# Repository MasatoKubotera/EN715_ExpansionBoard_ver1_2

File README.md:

<html lang="en">
  <head>
    <meta charset="uft-8">
    <meta name="author" content="Masato Kubotera">
  </head>
  <body>
    <h1>EN715 Expansion Board Ver. 1.2</h1>
    <h2>About EN715 Expansion Board</h2>
    <p>
      The EN715 Expansion Board is a circuit board to expand the functions of the Carrier Board for NVIDIA Jetson manufactured by AverMedia.<br>
      <br>
      Note that this is Ver. 1.2. For other versions, please refer to the following repositories.
      <ul>
        <li><a href="https://github.com/MasatoKubotera/EN715_ExpansionBoard_ver1_0">EN715 Expansion Board Ver. 1.0</a></li>
        <li><a href="https://github.com/MasatoKubotera/EN715_ExpansionBoard_ver1_1">EN715 Expansion Board Ver. 1.1</a></li>
      </ul>
      <h2>About Ver. 1.2</h2>
      <table>
        <tr>
          <td>
            <div align="center">
              under construction<br>
              
            </div>
          </td>
          <td>
            <div align="center">
              under construction<br>
              
            </div>
          </td>
        </tr>
        <tr>
          <td>
            <div align="center">
              PCB preview image
            </div>
          </td>
          <td>
            <div align="center">
              After component mounting
            </div>
          </td>    
        </tr>
      </table>
    <h2>Repository Contents</h2>
    <p>
    <dl>
      <dt>\image</dt>
      <dd>PCB preview images and capture of design screen</dd>
      <dt>\libraries</dt>
      <dd>Libraries used in Autodesk Eagle design</dd>
      <dt>Schematic.pdf</dt>
      <dd>Circuit diagram of this product</dd>
      <dt>BOM.txt</dt>
      <dd>Parts lists output from design data</dd>
      <dt>.brd</dt>
      <dd>Board wiring design file by Autodesk Eagle</dd>
      <dt>.sch</dt>
      <dd>Schematic design file by Autodesk Eagle</dd>
      <!--
      <dt>Gerber_data.zip</dt>
      <dd>Zip folder of Gerber format files for PCB manufacturing requests.</dd>
      -->
      <dt>LICENSE</dt>
      <dd>This is a license to use this product. Please confirm before use.</dd>
      <dt>.gitignore</dt>
      <dd>File to exclude cache files from management.</dd>
    </dl>
    </p>
    <h2>Documentation</h2>
      <p>
        <h3>BOM</h3>
          <table>
            <thead>
              <tr>
                <th> Eagle Design Parts # </th>
                <th> Q'ty </th>
                <th> Mfr. Product # </th>
                <th> Supplier </th>
                <th> Description </th>
              </tr>
            </thead>
            <tbody>
              <tr>
                <td> C1, C2, C3 </td>
                <td> 3 </td>
                <td> GRM188R6YA106MA73 </td>
                <td> <a href="https://akizukidenshi.com/catalog/g/gP-13161/">Akizuki</a> </td>
                <td> Multilayer Ceramic Capacitors SMD/SMT 10uF 35V 20% 0603 </td>
              </tr>
              <tr>
                <td> C4 </td>
                <td> 1 </td>
                <td> GRM188B11H103KA01 </td>
                <td> <a href="https://akizukidenshi.com/catalog/g/gP-13387/">Akizuki</a> </td>
                <td> Multilayer Ceramic Capacitors SMD/SMT 0.01uF 50V 10% 0603 </td>
              </tr>
              <tr>
                <td> C5, C6 </td>
                <td> 2 </td>
                <td> C1608C0G1H220J080AA </td>
                <td> <a href="https://www.mouser.jp/ProductDetail/TDK/C1608C0G1H220J080AA?qs=NRhsANhppD%2FvEAPMU6eN6g%3D%3D">Mouser</a> </td>
                <td> Multilayer Ceramic Capacitors SMD/SMT 22pF 50V 5% 0603 </td>
              </tr>
              <tr>
                <td> CH1 </td>
                <td> 1 </td>
                <td> FH-2x10SG </td>
                <td> <a href="https://akizukidenshi.com/catalog/g/gC-00083/">Akizuki</a> </td>
                <td> 2.54mm Pin Socket, 2 Row, 20 Pin </td>
              </tr>
              <tr>
                <td> CR1 </td>
                <td> 1 </td>
                <td> FA-238V 12.0000MB-K3 </td>
                <td> <a href="https://akizukidenshi.com/catalog/g/gP-05225/">Akizuki</a> </td>
                <td> Crystals 12.0000MHz 50ppm 10pF -40C +85C </td>
              </tr>
              <tr>
                <td> D1, D2, D3, D4, D5, D6, D7, D8, D9, D10 </td>
                <td> 10 </td>
                <td> CG0603MLC-05E </td>
                <td> <a href="https://www.mouser.jp/ProductDetail/Bourns/CG0603MLC-05E?qs=lDok7oSghXVLNKMK69q%252BFQ%3D%3D">Mouser</a> </td>
                <td> ESD Protectors 5V 0603 </td>
              </tr>
              <tr>
                <td> F1 </td>
                <td> 1 </td>
                <td> MF-MSMF050-2 </td>
                <td> <a href="https://www.mouser.jp/ProductDetail/Bourns/MF-MSMF050-2?qs=t3shhpq1i1DZ7OBD5kLNoA%3D%3D">Mouser</a> </td>
                <td> PTC Resettable Fuses 15V .5A-HD 100A MAX </td>
              </tr>
              <tr>
                <td> FL1, FL2, FL3, FL4, FL5 </td>
                <td> 5 </td>
                <td> BLM18SD220SN1D </td>
                <td> <a href="https://www.mouser.jp/ProductDetail/Murata-Electronics/BLM18SD220SN1D?qs=glnLrWX4TPq%2Fm8%2FdPQltLg%3D%3D">Mouser</a> </td>
                <td> Ferrite Beads 22 OHM 0603 </td>
              </tr>
              <tr>
                <td> IC1 </td>
                <td> 1 </td>
                <td> FE1.1S </td>
                <td> <a href="https://www.aitendo.com/product/16185">aitendo</a> </td>
                <td> USB Interface IC USB 2.0 Hi-Speed 4 Port Hub Controller </td>
              </tr>
              <tr>
                <td> LED1 </td>
                <td> 1 </td>
                <td> 150060VS86000 </td>
                <td> <a href="https://www.mouser.jp/ProductDetail/Wurth-Elektronik/150060VS86000?qs=GedFDFLaBXGW9qOjzZ1Hmw%3D%3D">Mouser</a> </td>
                <td> Standard LEDs - SMD Green 2V 20mA 573nm 0603 </td>
              </tr>
              <tr>
                <td> LED2, LED3, LED4, LED5, LED6 </td>
                <td> 5 </td>
                <td> 150060YS75000 </td>
                <td> <a href="https://www.mouser.jp/ProductDetail/Wurth-Elektronik/150060YS75000?qs=LlUlMxKIyB0nKmwefHgtZw%3D%3D">Mouser</a> </td>
                <td> Standard LEDs - SMD Yellow 2V 20mA 590nm 0603 </td>
              </tr>
              <tr>
                <td> M1 </td>
                <td> 1 </td>
                <td> SEN-15335 </td>
                <td> <a href="https://www.mouser.jp/ProductDetail/SparkFun/SEN-15335?qs=uwxL4vQweFMcls1MYZT00A%3D%3D">Mouser</a> </td>
                <td> 9-Axis MotionTracking Device Module </td>
              </tr>
              <tr>
                <td> M1 </td>
                <td> 1 </td>
                <td> 6604S-40 </td>
                <td> <a href="https://akizukidenshi.com/catalog/g/gP-01591/">Akizuki</a> </td>
                <td> 2.54mm Pin Socket Strip, Single Row </td>
              </tr>
              <tr>
                <td> M1 </td>
                <td> 1 </td>
                <td> PHA-1x40SG </td>
                <td> <a href="https://akizukidenshi.com/catalog/g/gC-06631/">Akizuki</a> </td>
                <td> 2.54mm Pin Header Strip, Straight, Single Row </td>
              </tr>
              <tr>
                <td> R1, R3, R4, R5 </td>
                <td> 4 </td>
                <td> RC0603FR-101KL </td>
                <td> <a href="https://www.mouser.jp/ProductDetail/YAGEO/RC0603FR-101KL?qs=EiqXWrxQq63MM0wzm69ZKg%3D%3D">Mouser</a> </td>
                <td> Thick Film Resistors - SMD 1 kOhms 100-200mW 1% 0603 </td>
              </tr>
              <tr>
                <td> R2 </td>
                <td> 1 </td>
                <td> RC0603FR-102K7L </td>
                <td> <a href="https://www.mouser.jp/ProductDetail/YAGEO/RC0603FR-102K7L?qs=Iqe6t0HYRD6Xaw3IgOqXnw%3D%3D">Mouser</a> </td>
                <td> Thick Film Resistors - SMD 2.7 kOhms 100-200 mW 1% 0603 </td>
              </tr>
              <tr>
                <td> USB1 </td>
                <td> 1 </td>
                <td> MUSB-5B-NE-S175 </td>
                <td> <a href="https://akizukidenshi.com/catalog/g/gC-05843/">Akizuki</a> </td>
                <td> Mini USB Connector 5P B type, Female, SMT type, without standoff </td>
              </tr>
              <tr>
                <td> USB2, USB3, USB4, USB5 </td>
                <td> 4 </td>
                <td> USB1046-GF-0190-L-B-A </td>
                <td> <a href="https://www.mouser.jp/ProductDetail/640-USB1046GF0190LBA">Mouser</a> </td>
                <td> USB Connectors USB2.0 A, Top Mount, SMT </td>
              </tr>
            </tbody>
          </table>
        <!--
        <h3>PCB Fabrication</h3>
          PCB(Printed Circuit Board) manufacturing was outsourced to <a href="https://www.elecrow.com/pcb-manufacturing.html">Elecrow</a>.<br>
          The custom specifications are as follows.
          <ul>
            <li>Layer : 2 layers</li>
            <li>Dimensions : 87 x 50</li>
            <li>PCB Qty : 10</li>
            <li>Different PCB Design : 1eg</li>
            <li>PCB Thickness : 1.6</li>
            <li>PCB Color : Black</li>
            <li>Surface Finish : HASL Lead Free</li>
            <li>Castellated Hole : No</li>
            <li>Copper Weight : 1oz</li>
            <li>PCB Stencil : Stencil 15cm X 15cm no frame</li>
          </ul>
          The data used to order fabrication are as follows.
          <ul>
            <li>Eagle design rule : <a href="https://www.elecrow.com/download/Elecrow_PCB_eagle_rule.zip">Elecrow Eagle Design Rule</a></li>
            <li>Eagle CAM file : <a href="https://www.elecrow.com/download/Elecrow_Gerber_Generater_DrillAlign.zip">Elecrow CAM file</a></li>
            <li>Gerber format data : <a href="/Gerber_data.zip">Gerber_data.zip</a></li>
          </ul>
      </p>
      -->
    <h2>Contact</h2>
    <p>
    If you have any questions, please contact MasatoKubotera, the product's designer, by E-mail.<br>
    E-mail : <a href="mailto:masatokubotera06@yahoo.co.jp">masatokubotera06@yahoo.co.jp</a>
    </p>
    <h2>License Information</h2>
    <p>
      This product is open source.<br>
      Please review the <a href="/LICENSE">LICENSE file</a> for license information.<br>
      <br>
      <strong>EN715 Expansion Board Ver. 1.2</strong> by Masato Kubotera is licensed under a <a href="http://creativecommons.org/licenses/by-nc-sa/4.0/">Creative Commons Attribution-NonCommercial-ShareAlike 4.0 International License</a>.
    </p>
  </body>
</html>

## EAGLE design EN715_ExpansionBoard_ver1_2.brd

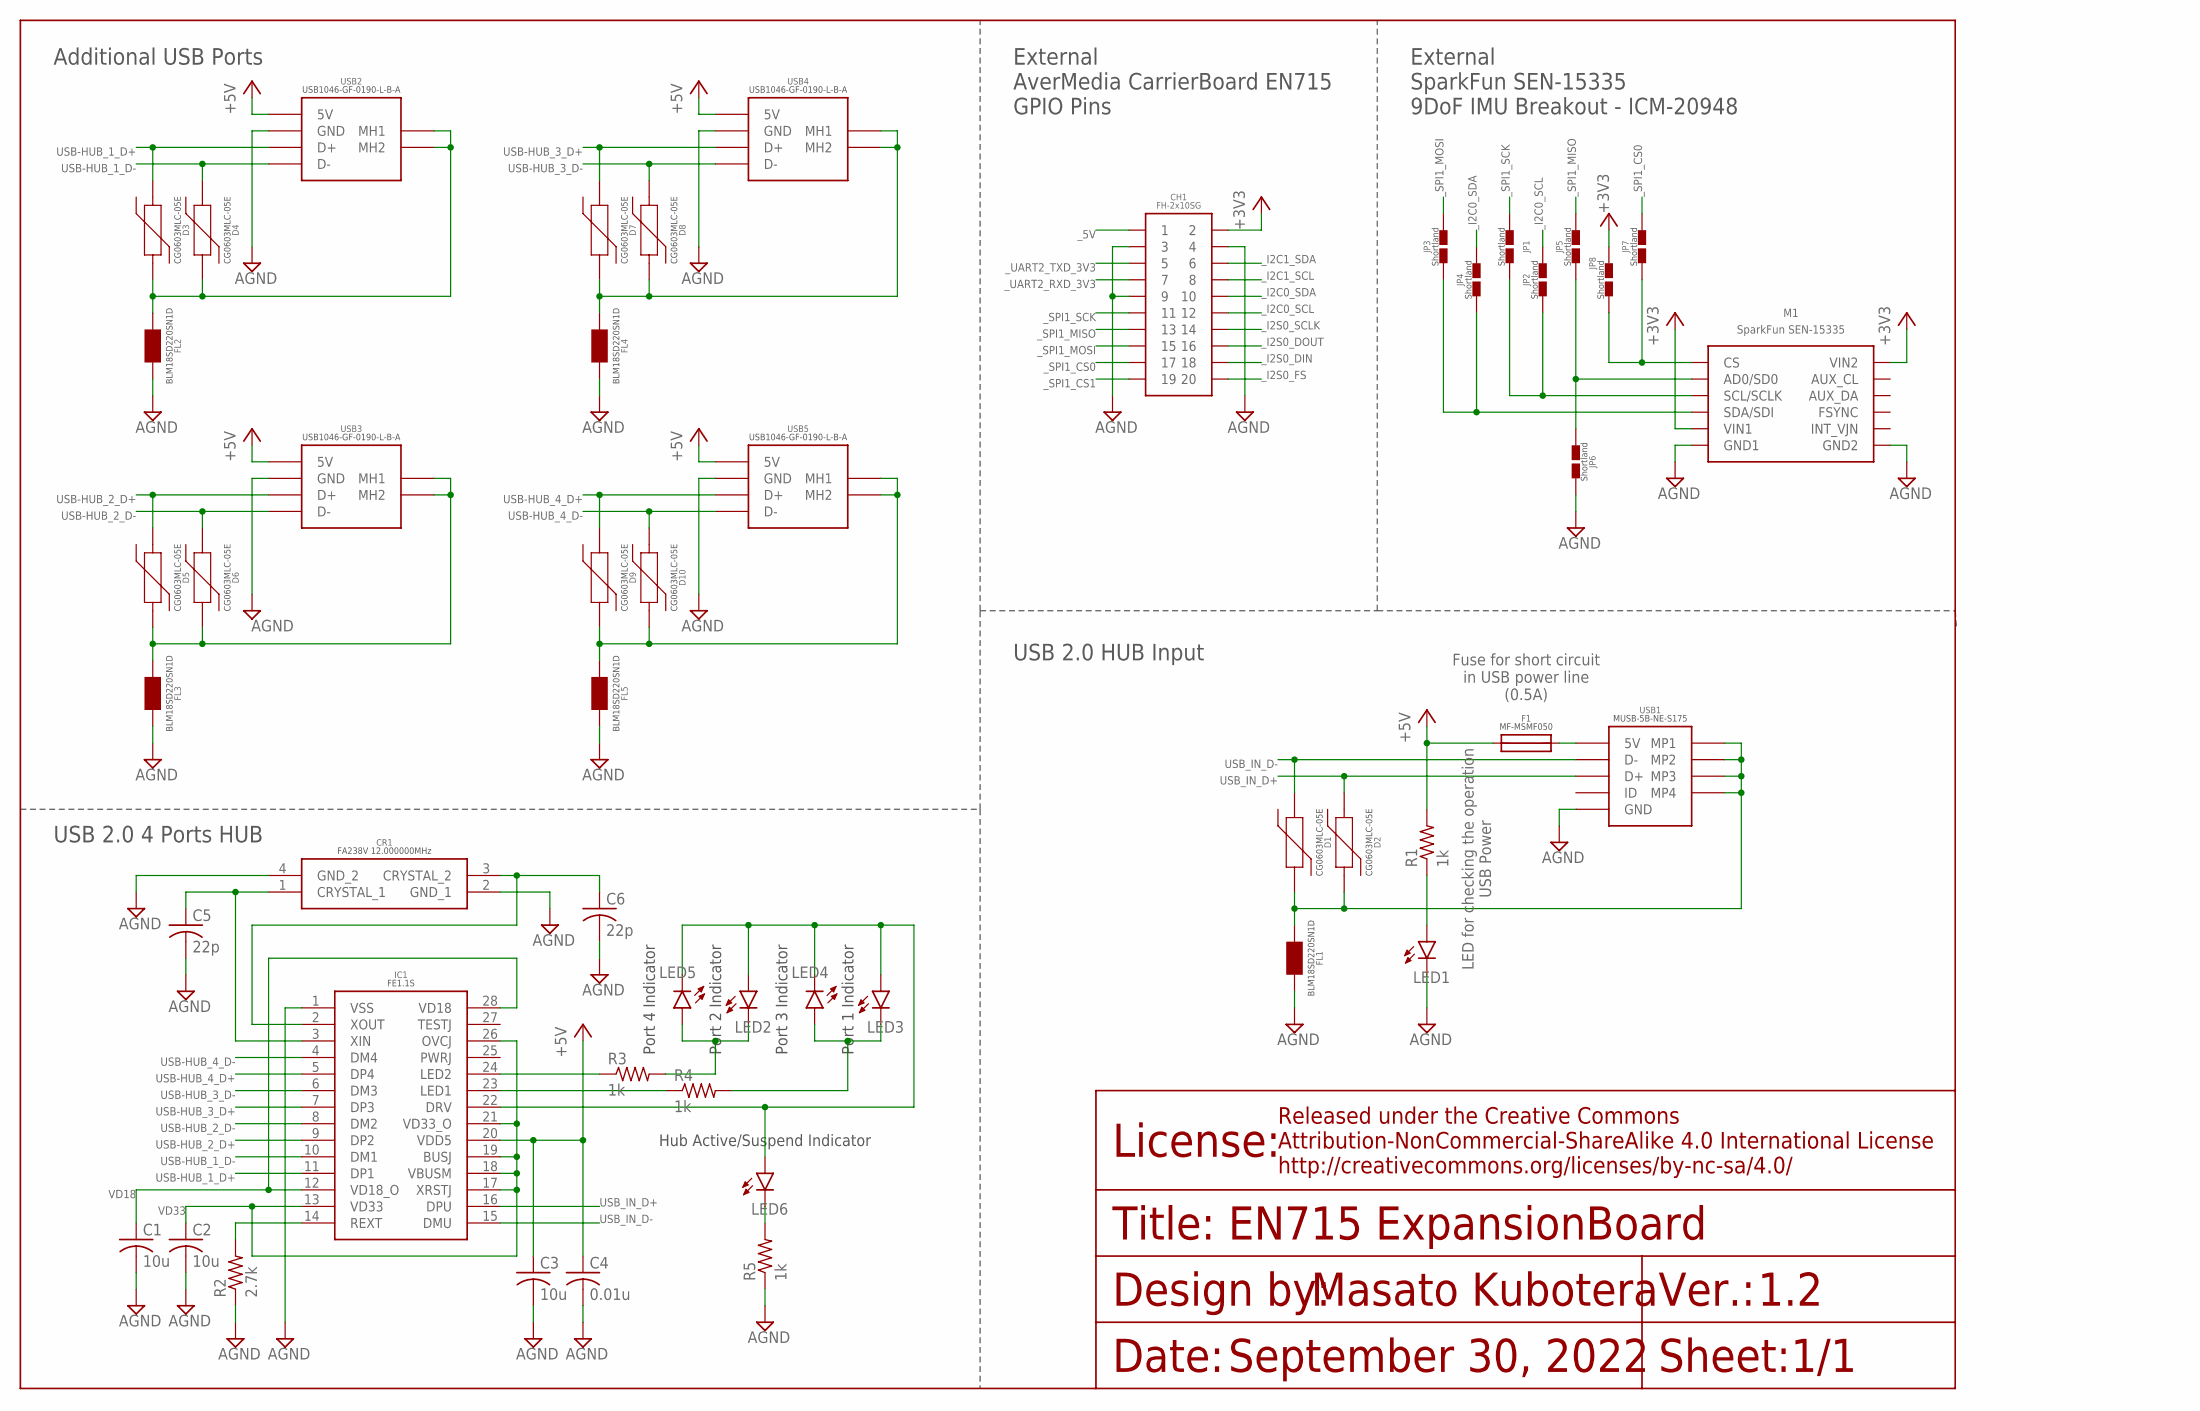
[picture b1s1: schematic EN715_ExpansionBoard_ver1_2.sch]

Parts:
C1, C2, C3: 10u; C0603
C4: 0.01u; C0603
C5, C6: 22p; C0603
CH1: 2X10
CR1: FA238V_12.000000MHZ; FA238V
D1, D2, D3, D4, D5, D6, D7, D8, D9, D10: CG0603MLC-05E
F1: MF-MSMF050
FL1, FL2, FL3, FL4, FL5: BLM18SD220SN1D
IC1: FE1.1S
JP1, JP2, JP3, JP4, JP5, JP6, JP7, JP8: SHORTLAND
LED1, LED2, LED3, LED4, LED5, LED6: LEDSML0603; SML0603
M1: SPARKFUN_SEN-15335
R1, R3, R4, R5: 1k; R0603
R2: 2.7k; R0603
USB1: MINI_USB_B_SMD
USB2, USB3, USB4, USB5: USB_A_X1_SMD

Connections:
+3V3: CH1.2, JP8.2, M1.VIN (VIN1), M1.VIN1 (VIN2)
+5V: C3.1, C4.1, F1.1, IC1.20 (VDD5), R1.2, USB2.1 (5V), USB3.1 (5V), USB4.1 (5V), USB5.1 (5V)
AGND: C1.2, C2.2, C3.2, C4.2, C5.2, C6.2, CH1.3, CH1.4, CH1.9, CR1.2 (GND_1), CR1.4 (GND_2), FL1.2, FL2.2, FL3.2, FL4.2, FL5.2, IC1.1 (VSS), JP6.2, LED1.C, M1.GND1, M1.GND2, R2.1, R5.1, USB1.5 (GND), USB2.4 (GND), USB3.4 (GND), USB4.4 (GND), USB5.4 (GND)
B_FUSE_USB_MINI_B: F1.2, USB1.1 (5V)
FE1.1S_DRV: IC1.22 (DRV), LED2.A, LED3.A, LED4.C, LED5.C, LED6.A
FE1.1S_DRV_LED_A: LED6.C, R5.2
FE1.1S_LED_1_A: LED3.C, LED4.A, R4.2
FE1.1S_LED_1_B: IC1.23 (LED1), R4.1
FE1.1S_LED_2_A: LED2.C, LED5.A, R3.2
FE1.1S_LED_2_B: IC1.24 (LED2), R3.1
IMU_AD0/SD0: JP5.1, JP6.1, M1.AD0/SD0
IMU_SCL/SCLK: JP1.1, JP2.1, M1.SCL/SCLK
IMU_SDA/SDI: JP3.1, JP4.1, M1.SDA/SDI
LED_USBIN: LED1.A, R1.1
MPU9250_CS: JP7.1, JP8.1, M1.CS
REXT_FE1.1S: IC1.14 (REXT), R2.2
USB-HUB_1_D+: D3.1, IC1.11 (DP1), USB2.3 (D+)
USB-HUB_1_D-: D4.1, IC1.10 (DM1), USB2.2 (D-)
USB-HUB_2_D+: D5.1, IC1.9 (DP2), USB3.3 (D+)
USB-HUB_2_D-: D6.1, IC1.8 (DM2), USB3.2 (D-)
USB-HUB_3_D+: D7.1, IC1.7 (DP3), USB4.3 (D+)
USB-HUB_3_D-: D8.1, IC1.6 (DM3), USB4.2 (D-)
USB-HUB_4_D+: D9.1, IC1.5 (DP4), USB5.3 (D+)
USB-HUB_4_D-: D10.1, IC1.4 (DM4), USB5.2 (D-)
USB_A_1_SHIELD: D3.2, D4.2, FL2.1, USB2.MH1, USB2.MH2
USB_A_2_SHIELD: D5.2, D6.2, FL3.1, USB3.MH1, USB3.MH2
USB_A_3_SHIELD: D7.2, D8.2, FL4.1, USB4.MH1, USB4.MH2
USB_A_4_SHIELD: D9.2, D10.2, FL5.1, USB5.MH1, USB5.MH2
USB_IN_D+: D2.1, IC1.16 (DPU), USB1.3 (D+)
USB_IN_D-: D1.1, IC1.15 (DMU), USB1.2 (D-)
USB_MINI_B_SHIELD: D1.2, D2.2, FL1.1, USB1.MP1, USB1.MP2, USB1.MP3, USB1.MP4
VD18: C1.1, IC1.12 (VD18_O), IC1.28 (VD18)
VD33: C2.1, IC1.13 (VD33), IC1.17 (XRSTJ), IC1.18 (VBUSM), IC1.19 (BUSJ), IC1.21 (VD33_O), IC1.26 (OVCJ)
XIN_FE1.1S: C5.1, CR1.1 (CRYSTAL_1), IC1.3 (XIN)
XOUT_FE1.1S: C6.1, CR1.3 (CRYSTAL_2), IC1.2 (XOUT)
_5V: CH1.1
_I2C0_SCL: CH1.12, JP2.2
_I2C0_SDA: CH1.10, JP4.2
_I2C1_SCL: CH1.8
_I2C1_SDA: CH1.6
_I2S0_DIN: CH1.18
_I2S0_DOUT: CH1.16
_I2S0_FS: CH1.20
_I2S0_SCLK: CH1.14
_SPI1_CS0: CH1.17, JP7.2
_SPI1_CS1: CH1.19
_SPI1_MISO: CH1.13, JP5.2
_SPI1_MOSI: CH1.15, JP3.2
_SPI1_SCK: CH1.11, JP1.2
_UART2_RXD_3V3: CH1.7
_UART2_TXD_3V3: CH1.5

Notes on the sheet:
Hub Active/Suspend Indicator
Port 1 Indicator
Port 2 Indicator
USB 2.0 4 Ports HUB
Additional USB Ports
USB 2.0 HUB Input
Fuse for short circuit in USB power line (0.5A)
LED for checking the operation USB Power
External SparkFun SEN-15335 9DoF IMU Breakout - ICM-20948
Port 3 Indicator
Port 4 Indicator
1.2
1/1
September 30, 2022
EN715 ExpansionBoard
External AverMedia CarrierBoard EN715 GPIO Pins

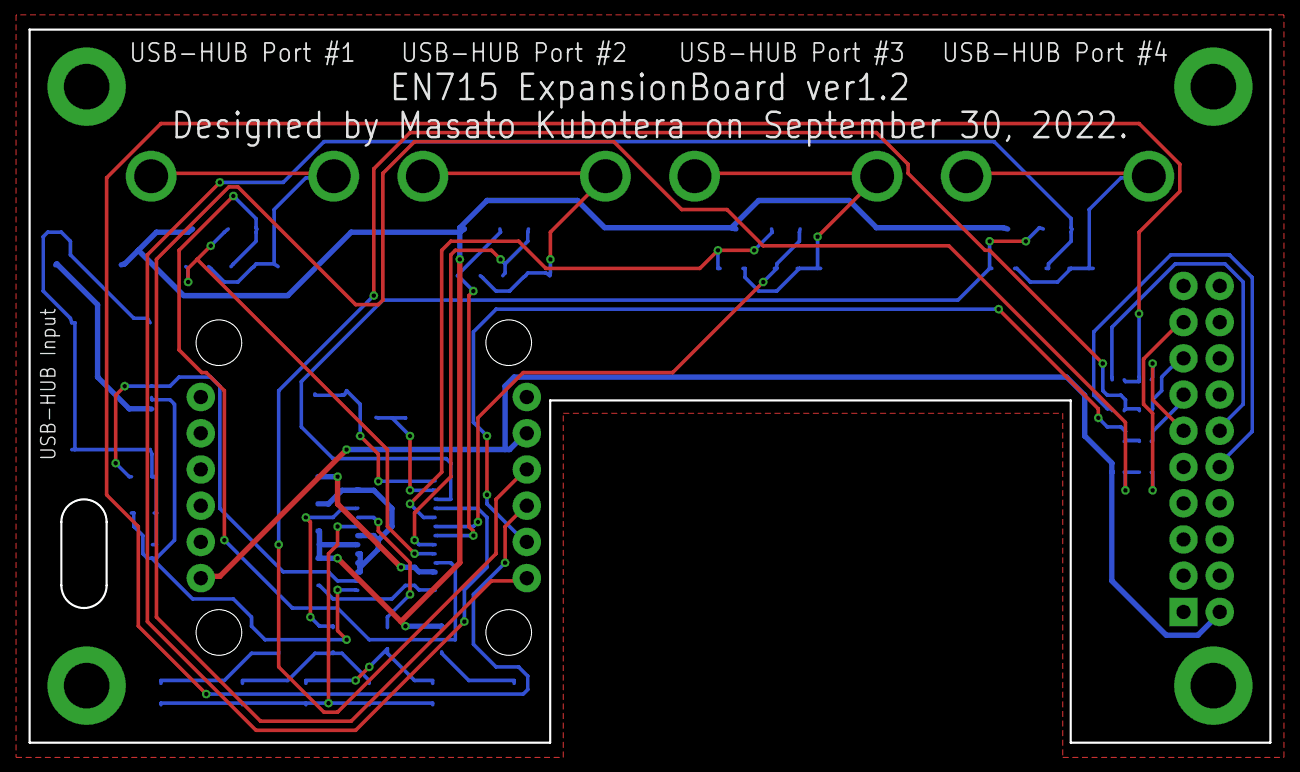
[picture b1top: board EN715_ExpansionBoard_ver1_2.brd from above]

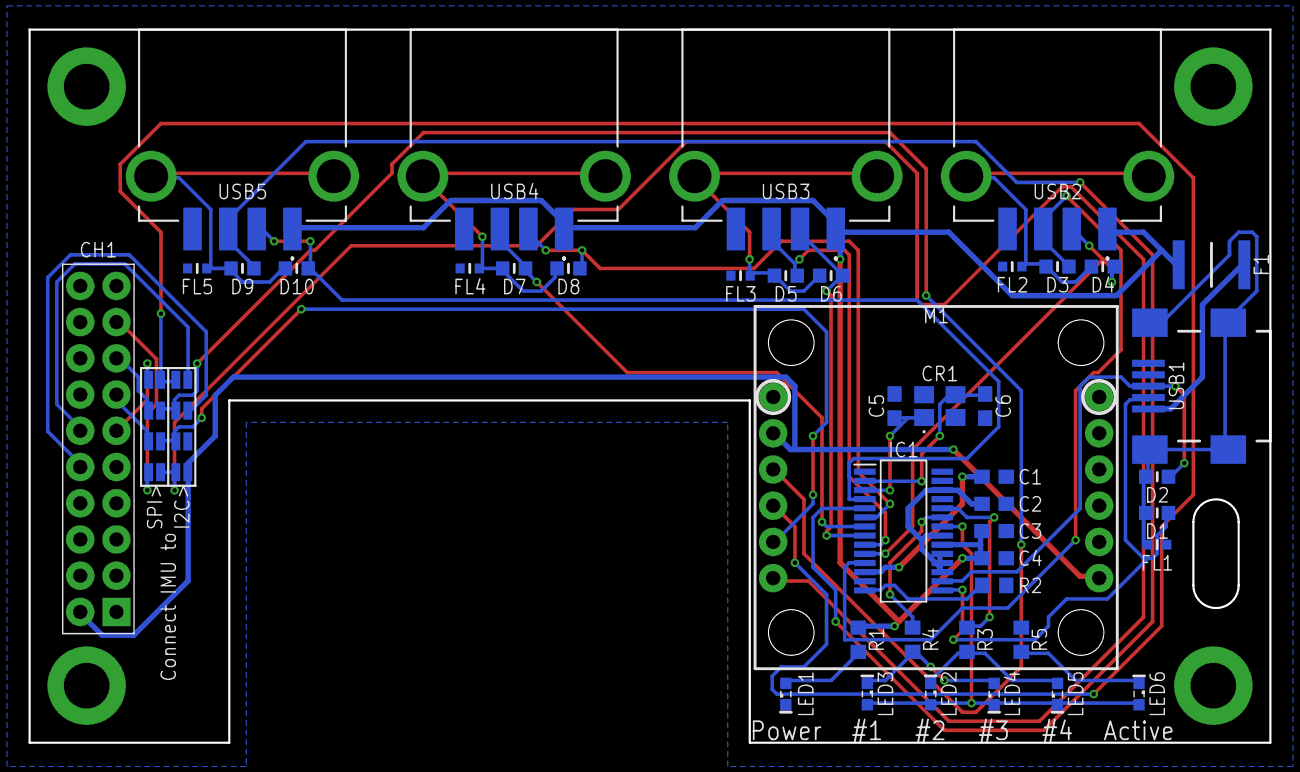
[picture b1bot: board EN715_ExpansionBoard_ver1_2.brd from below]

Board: 2 copper layers, 87.0 x 50.0 mm, 50 parts (50 on the bottom side), 41 nets.

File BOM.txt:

Partlist exported from C:/Users/MasatoKubotera/Documents/citbrains/EN715_ExpansionBoard_ver1_2/EN715_ExpansionBoard_ver1_2.sch at 2022/10/02 23:37

Qty Value               Device              Package            Parts                                   Description                
6                       LEDSML0603          SML0603            LED1, LED2, LED3, LED4, LED5, LED6      LED                        
1   0.01u               C-USC0603           C0603              C4                                      CAPACITOR, American symbol 
3   10u                 C-USC0603           C0603              C1, C2, C3                              CAPACITOR, American symbol 
4   1k                  R-US_R0603          R0603              R1, R3, R4, R5                          RESISTOR, American symbol  
1   2.7k                R-US_R0603          R0603              R2                                      RESISTOR, American symbol  
2   22p                 C-USC0603           C0603              C5, C6                                  CAPACITOR, American symbol 
1   2X10                2X10                2X10               CH1                                                                
5   BLM18SD220SN1D      BLM18SD220SN1D      BLM18SD220SN1D     FL1, FL2, FL3, FL4, FL5                                            
10  CG0603MLC-05E       CG0603MLC-05E       CG0603MLC-05E      D1, D2, D3, D4, D5, D6, D7, D8, D9, D10                            
1   FA238V_12.000000MHZ FA238V_12.000000MHZ FA238V             CR1                                                                
1   FE1.1S              FE1.1S              FE1.1S             IC1                                                                
1   MF-MSMF050          MF-MSMF050          MF-MSMF050         F1                                                                 
1   MINI_USB_B_SMD      MINI_USB_B_SMD      MINI_USB_B_SMD     USB1                                                               
8   SHORTLAND           SHORTLAND           SHORTLAND          JP1, JP2, JP3, JP4, JP5, JP6, JP7, JP8                             
1   SPARKFUN_SEN-15335  SPARKFUN_SEN-15335  SPARKFUN_SEN-15335 M1                                                                 
4   USB_A_X1_SMD        USB_A_X1_SMD        USB_A_X1_SMD       USB2, USB3, USB4, USB5

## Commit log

2022-09-19 Schematic drawing with IMU changed to SparkFun SEN-1533
2022-09-20 Organizing Files
2022-09-23 Update LICENSE
2022-10-02 Add information for production

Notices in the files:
parts and their libraries:
Frame: Released under the Creative Commons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
